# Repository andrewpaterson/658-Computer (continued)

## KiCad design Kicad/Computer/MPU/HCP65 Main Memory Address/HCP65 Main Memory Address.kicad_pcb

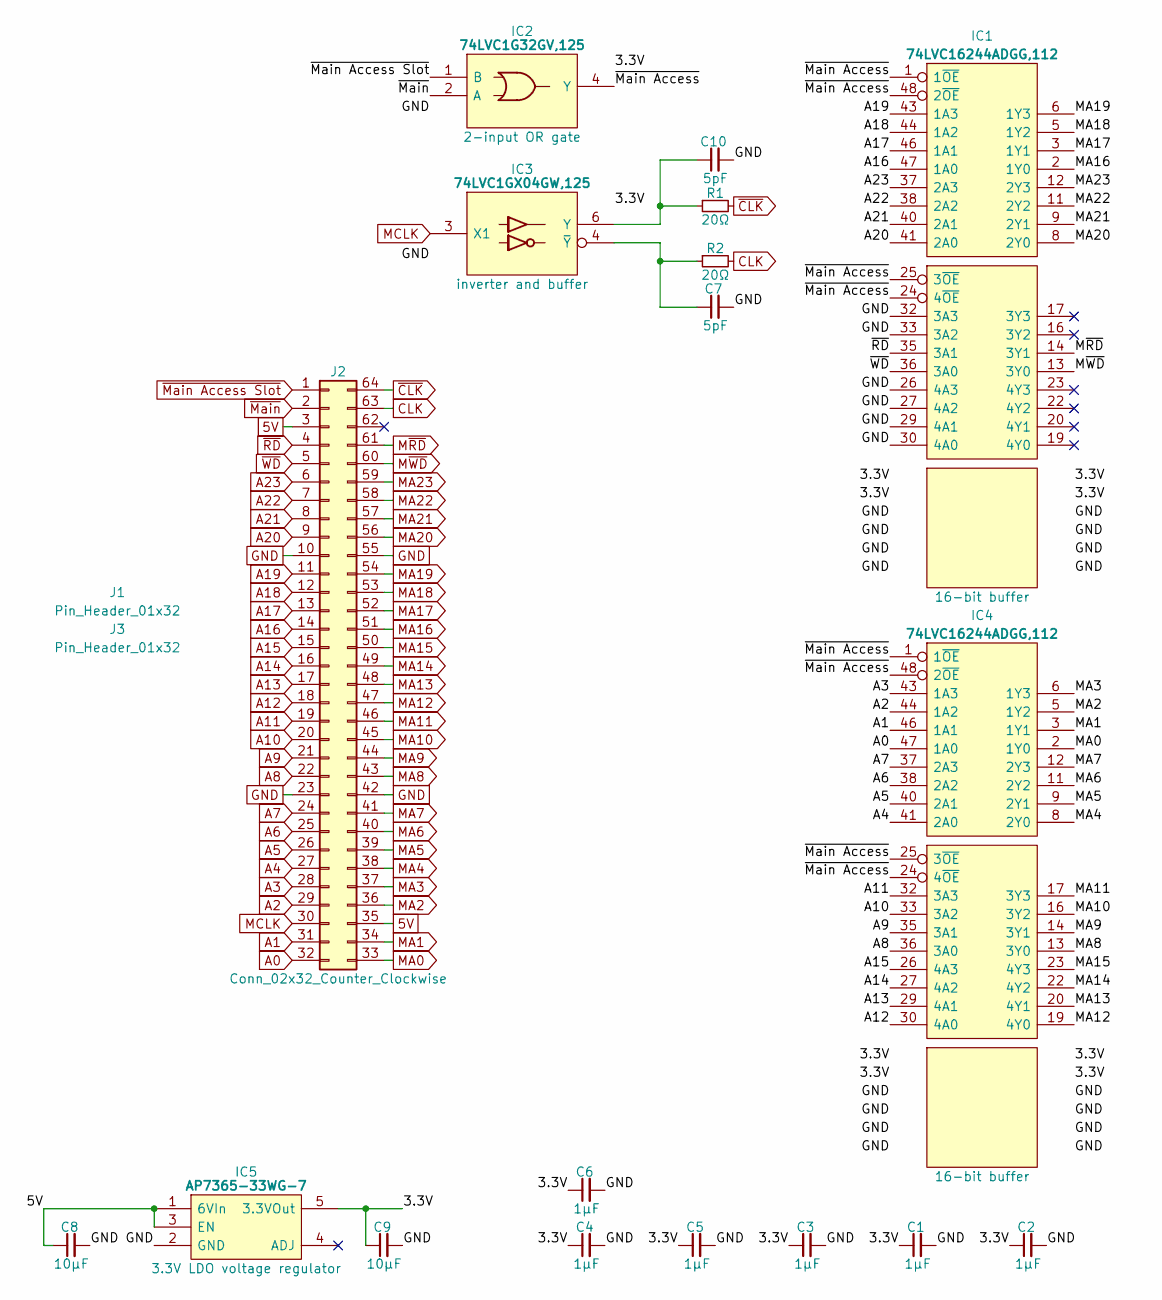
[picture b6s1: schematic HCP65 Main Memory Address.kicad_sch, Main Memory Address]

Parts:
C1, C2, C3, C4, C5, C6: 1μF; C_0805
C7, C10: 5pF; C_0805
C8, C9: 10µF; C_0805
IC1, IC4: 74LVC16244ADGG,112; 74LVC16244ADGG112; Manufacturer_Part_Number 74LVC16244ADGG,112; Mouser Part Number 771-74LVC16244DG
IC2: 74LVC1G32GV,125; SOT95P275X110-5N; Manufacturer_Part_Number 74LVC1G32GV,125; Mouser Part Number 771-LVC1G32GV125
IC3: 74LVC1GX04GW,125; SOP65P210X110-6N; Manufacturer_Part_Number 74LVC1GX04GW,125; Mouser Part Number 771-74LVC1GX04GW-G
IC5: AP7365-33WG-7; SOT95P285X130-5N; Manufacturer_Part_Number AP7365-33WG-7; Mouser Part Number 621-AP7365-33WG-7
J1, J3: Pin_Header_01x32; PinHeader_1x32_P2.54mm_Vertical
J2: Conn_02x32_Counter_Clockwise; DIP-64_Board_W15.24mm
R1, R2: 20Ω; R_0805

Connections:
5V: C8.1, IC5.1 (6VIn), IC5.3 (EN), J2.3, J2.35
/3.3V: C1.1, C2.1, C3.1, C4.1, C5.1, C6.1, C9.1, IC1.7 (3V), IC1.18 (3V), IC1.31 (3V), IC1.42 (3V), IC2.5 (3V), IC3.5 (3V), IC4.7 (3V), IC4.18 (3V), IC4.31 (3V), IC4.42 (3V), IC5.5 (3.3VOut)
/~Main Access: IC1.1 (1~OE), IC1.24 (4~OE), IC1.25 (3~OE), IC1.48 (2~OE), IC2.4 (Y), IC4.1 (1~OE), IC4.24 (4~OE), IC4.25 (3~OE), IC4.48 (2~OE)
A0: IC4.47 (1A0), J2.32
A1: IC4.46 (1A1), J2.31
A2: IC4.44 (1A2), J2.29
A3: IC4.43 (1A3), J2.28
A4: IC4.41 (2A0), J2.27
A5: IC4.40 (2A1), J2.26
A6: IC4.38 (2A2), J2.25
A7: IC4.37 (2A3), J2.24
A8: IC4.36 (3A0), J2.22
A9: IC4.35 (3A1), J2.21
A10: IC4.33 (3A2), J2.20
A11: IC4.32 (3A3), J2.19
A12: IC4.30 (4A0), J2.18
A13: IC4.29 (4A1), J2.17
A14: IC4.27 (4A2), J2.16
A15: IC4.26 (4A3), J2.15
A16: IC1.47 (1A0), J2.14
A17: IC1.46 (1A1), J2.13
A18: IC1.44 (1A2), J2.12
A19: IC1.43 (1A3), J2.11
A20: IC1.41 (2A0), J2.9
A21: IC1.40 (2A1), J2.8
A22: IC1.38 (2A2), J2.7
A23: IC1.37 (2A3), J2.6
CLK: J2.63, R2.2
GND: C1.2, C2.2, C3.2, C4.2, C5.2, C6.2, C7.2, C8.2, C9.2, C10.2, IC1.4 (GND), IC1.10 (GND), IC1.15 (GND), IC1.21 (GND), IC1.26 (4A3), IC1.27 (4A2), IC1.28 (GND), IC1.29 (4A1), IC1.30 (4A0), IC1.32 (3A3), IC1.33 (3A2), IC1.34 (GND), IC1.39 (GND), IC1.45 (GND), IC2.3 (GND), IC3.2 (GND), IC4.4 (GND), IC4.10 (GND), IC4.15 (GND), IC4.21 (GND), IC4.28 (GND), IC4.34 (GND), IC4.39 (GND), IC4.45 (GND), IC5.2 (GND), J2.10, J2.23, J2.42, J2.55
MA0: IC4.2 (1Y0), J2.33
MA1: IC4.3 (1Y1), J2.34
MA2: IC4.5 (1Y2), J2.36
MA3: IC4.6 (1Y3), J2.37
MA4: IC4.8 (2Y0), J2.38
MA5: IC4.9 (2Y1), J2.39
MA6: IC4.11 (2Y2), J2.40
MA7: IC4.12 (2Y3), J2.41
MA8: IC4.13 (3Y0), J2.43
MA9: IC4.14 (3Y1), J2.44
MA10: IC4.16 (3Y2), J2.45
MA11: IC4.17 (3Y3), J2.46
MA12: IC4.19 (4Y0), J2.47
MA13: IC4.20 (4Y1), J2.48
MA14: IC4.22 (4Y2), J2.49
MA15: IC4.23 (4Y3), J2.50
MA16: IC1.2 (1Y0), J2.51
MA17: IC1.3 (1Y1), J2.52
MA18: IC1.5 (1Y2), J2.53
MA19: IC1.6 (1Y3), J2.54
MA20: IC1.8 (2Y0), J2.56
MA21: IC1.9 (2Y1), J2.57
MA22: IC1.11 (2Y2), J2.58
MA23: IC1.12 (2Y3), J2.59
MCLK: IC3.3 (X1), J2.30
M~RD: IC1.14 (3Y1), J2.61
M~WD: IC1.13 (3Y0), J2.60
unnamed: C10.1, IC3.6 (Y), R1.1
unnamed: C7.1, IC3.4 (~Y), R2.1
~CLK: J2.64, R1.2
~Main Access Slot: IC2.1 (B), J2.1
~Main: IC2.2 (A), J2.2
~RD: IC1.35 (3A1), J2.4
~WD: IC1.36 (3A0), J2.5

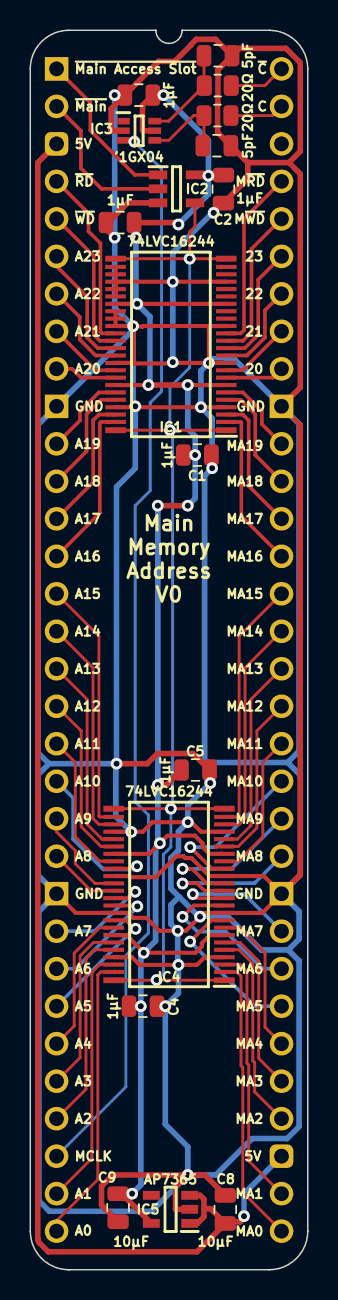
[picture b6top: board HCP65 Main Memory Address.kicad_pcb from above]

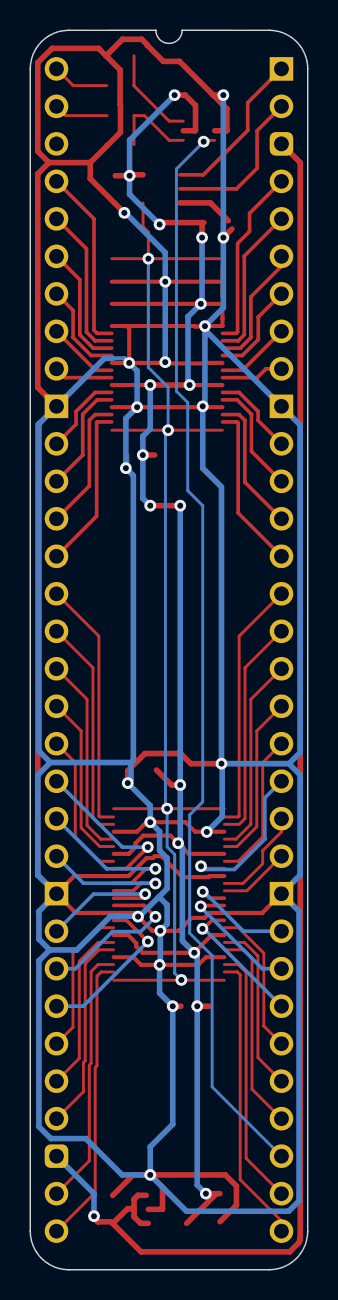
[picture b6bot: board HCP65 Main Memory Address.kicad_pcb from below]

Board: 2 copper layers, 18.8 x 84.0 mm, 20 parts (2 on the bottom side), 63 nets.

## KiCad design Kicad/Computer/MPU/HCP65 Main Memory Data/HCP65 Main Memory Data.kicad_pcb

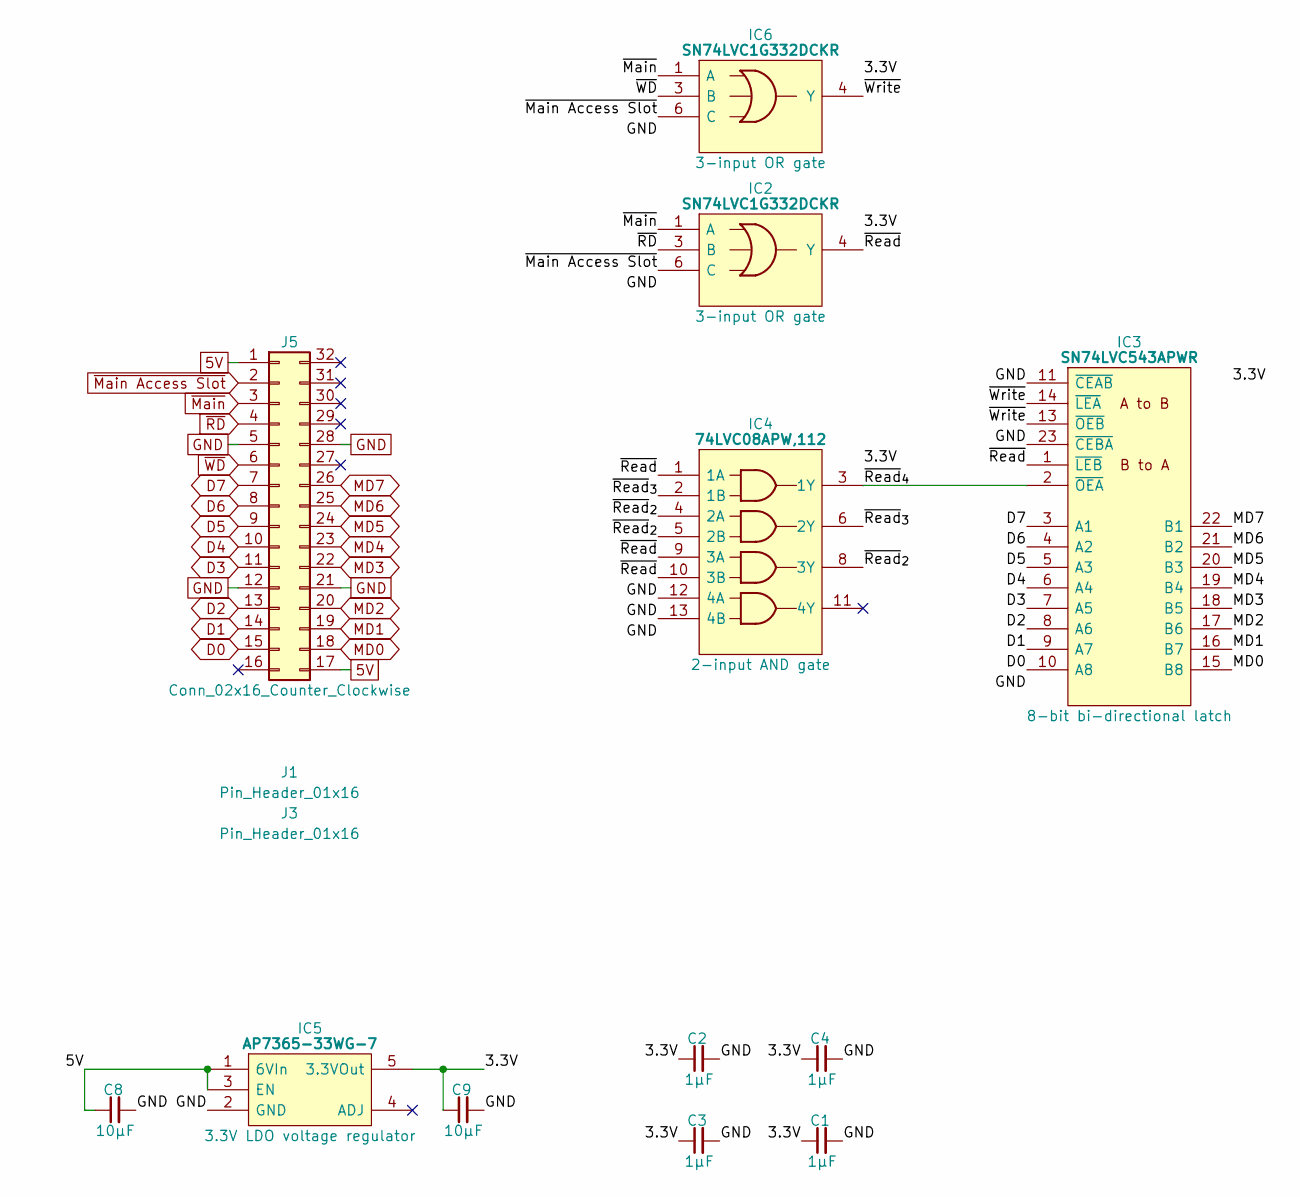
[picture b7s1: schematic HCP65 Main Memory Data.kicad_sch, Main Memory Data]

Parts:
C1, C2, C3, C4: 1μF; C_0805
C8, C9: 10µF; C_0805
IC2, IC6: SN74LVC1G332DCKR; SOT65P210X110-6N; Mouser Part Number 595-SN74LVC1G332DCKR
IC3: SN74LVC543APWR; SOP65P640X120-24N; Mouser Part Number 595-SN74LVC543APWR
IC4: 74LVC08APW,112; SOP65P640X110-14N; Manufacturer_Part_Number 74LVC08APW,112; Mouser Part Number 771-74LVC08APW
IC5: AP7365-33WG-7; SOT95P285X130-5N; Manufacturer_Part_Number AP7365-33WG-7; Mouser Part Number 621-AP7365-33WG-7
J1, J3: Pin_Header_01x16; PinHeader_1x16_P2.54mm_Vertical
J5: Conn_02x16_Counter_Clockwise; DIP-32_Board_W15.24mm

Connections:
5V: C8.1, IC5.1 (6VIn), IC5.3 (EN), J5.1, J5.17
/3.3V: C1.1, C2.1, C3.1, C4.1, C9.1, IC2.5 (3V), IC3.24 (3V), IC4.14 (3V), IC5.5 (3.3VOut), IC6.5 (3V)
/~Read: IC2.4 (Y), IC3.1 (~LEB), IC4.1 (1A), IC4.9 (3A), IC4.10 (3B)
/~Read_{2}: IC4.4 (2A), IC4.5 (2B), IC4.8 (3Y)
/~Read_{3}: IC4.2 (1B), IC4.6 (2Y)
/~Read_{4}: IC3.2 (~OEA), IC4.3 (1Y)
/~Write: IC3.13 (~OEB), IC3.14 (~LEA), IC6.4 (Y)
D0: IC3.10 (A8), J5.15
D1: IC3.9 (A7), J5.14
D2: IC3.8 (A6), J5.13
D3: IC3.7 (A5), J5.11
D4: IC3.6 (A4), J5.10
D5: IC3.5 (A3), J5.9
D6: IC3.4 (A2), J5.8
D7: IC3.3 (A1), J5.7
GND: C1.2, C2.2, C3.2, C4.2, C8.2, C9.2, IC2.2 (GND), IC3.11 (~CEAB), IC3.12 (GND), IC3.23 (~CEBA), IC4.7 (GND), IC4.12 (4A), IC4.13 (4B), IC5.2 (GND), IC6.2 (GND), J5.5, J5.12, J5.21, J5.28
MD0: IC3.15 (B8), J5.18
MD1: IC3.16 (B7), J5.19
MD2: IC3.17 (B6), J5.20
MD3: IC3.18 (B5), J5.22
MD4: IC3.19 (B4), J5.23
MD5: IC3.20 (B3), J5.24
MD6: IC3.21 (B2), J5.25
MD7: IC3.22 (B1), J5.26
~Main Access Slot: IC2.6 (C), IC6.6 (C), J5.2
~Main: IC2.1 (A), IC6.1 (A), J5.3
~RD: IC2.3 (B), J5.4
~WD: IC6.3 (B), J5.6

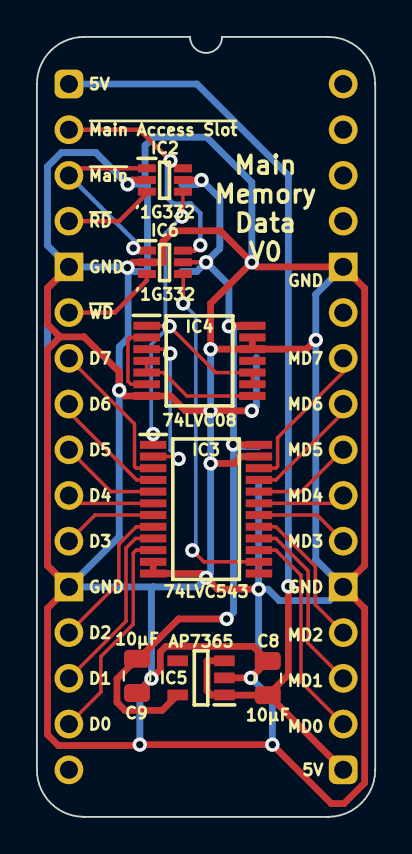
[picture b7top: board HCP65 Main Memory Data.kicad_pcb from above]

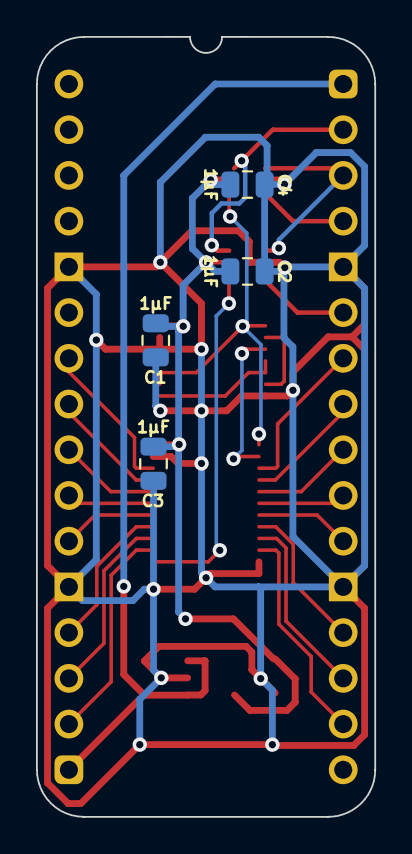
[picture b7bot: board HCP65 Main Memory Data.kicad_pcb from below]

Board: 2 copper layers, 18.8 x 43.3 mm, 14 parts (6 on the bottom side), 28 nets.

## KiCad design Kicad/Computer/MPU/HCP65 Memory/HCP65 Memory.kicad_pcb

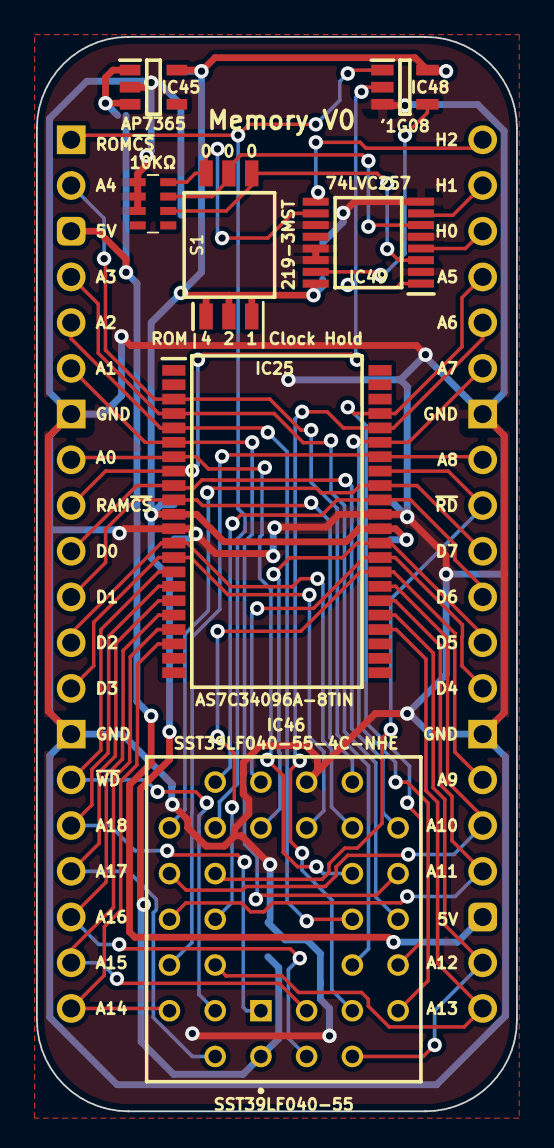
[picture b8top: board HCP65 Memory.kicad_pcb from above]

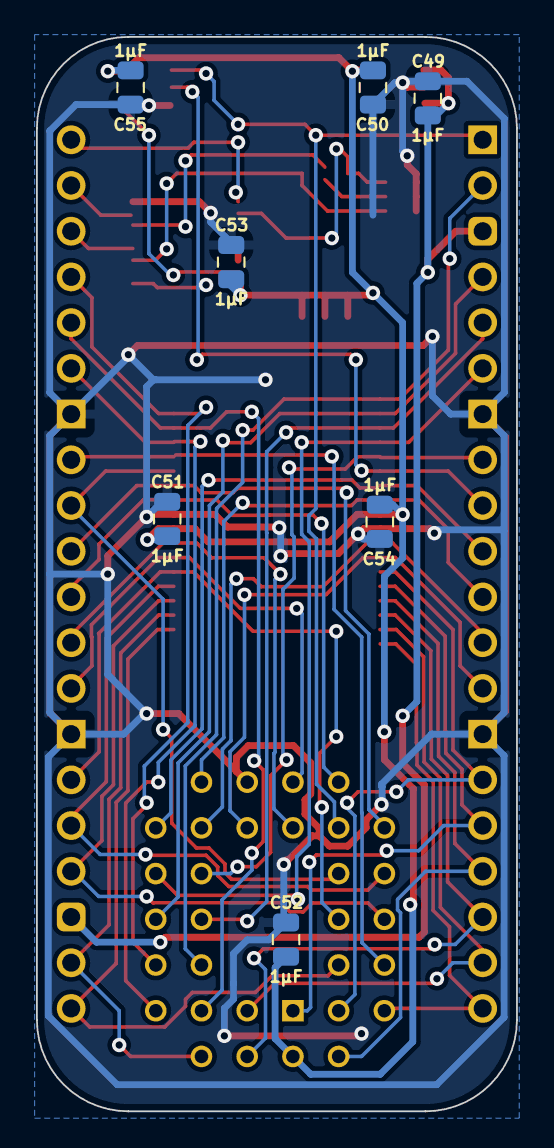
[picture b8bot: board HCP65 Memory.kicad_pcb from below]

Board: 2 copper layers, 26.7 x 59.7 mm, 15 parts (7 on the bottom side), 41 nets.

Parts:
C49, C50, C51, C52, C53, C54, C55: 1μF; C_0805
IC25: AS7C34096A-8TIN; SOP80P1176X120-44N
IC45: AP7365-33WG-7; SOT95P285X130-5N
IC46: SST39LF040-55-4C-NHE; 5408803224008
IC48: 74LVC1G08GV,125; SOT95P275X110-5N
IC49: 74LVC257APW,118; SOP65P640X110-16N
J8: Conn_02x20_Counter_Clockwise; DIP-40_Board_W22.86mm
RN3: CAY16-103J4LF; CAY16-J4
S1: 219-3MST; SOIC127P844X265-6N

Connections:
/Memory Board/3.3V: C50.1, C51.1, C52.1, C53.1, C54.1, C55.1, IC25.11 (3V), IC25.33 (3V), IC45.5 (VOUT), IC46.32 (3V), IC48.5 (3V), IC49.16 (3V), S1.1, S1.2, S1.3
/Memory Board/5V: C49.1, IC45.1 (VIN), IC45.3 (EN), J8.3, J8.23
/Memory Board/A0: IC25.7 (A0), IC46.12 (A0), J8.8
/Memory Board/A1: IC25.6 (A1), IC46.11 (A1), J8.6
/Memory Board/A2: IC25.5 (A2), IC46.10 (A2), J8.5
/Memory Board/A3: IC25.4 (A3), IC46.9 (A3), J8.4
/Memory Board/A4: IC25.3 (A4), IC46.8 (A4), J8.2
/Memory Board/A5: IC25.41 (A5), IC46.7 (A5), J8.37
/Memory Board/A6: IC25.40 (A6), IC46.6 (A6), J8.36
/Memory Board/A7: IC25.39 (A7), IC46.5 (A7), J8.35
/Memory Board/A8: IC25.38 (A8), IC46.27 (A8), J8.33
/Memory Board/A9: IC25.30 (A9), IC46.26 (A9), J8.26
/Memory Board/A10: IC25.29 (A10), IC46.23 (A10), J8.25
/Memory Board/A11: IC25.28 (A11), IC46.25 (A11), J8.24
/Memory Board/A12: IC25.27 (A12), IC46.4 (A12), J8.22
/Memory Board/A13: IC25.26 (A13), IC46.28 (A13), J8.21
/Memory Board/A14: IC25.20 (A14), IC46.29 (A14), J8.20
/Memory Board/A15: IC25.19 (A15), IC46.3 (A15), J8.19
/Memory Board/A16: IC25.18 (A16), IC46.2 (A16), J8.18
/Memory Board/A17: IC25.17 (A17), IC46.30 (A17), J8.17
/Memory Board/A18: IC25.16 (A18), IC46.1 (A18), J8.16
/Memory Board/CH0_{OUT}: IC49.4 (1Y), J8.38
/Memory Board/CH1_{OUT}: IC49.7 (2Y), J8.39
/Memory Board/CH2_{OUT}: IC49.9 (3Y), J8.40
/Memory Board/D0: IC25.9 (DQ0), IC46.13 (DQ0), J8.10
/Memory Board/D1: IC25.10 (DQ1), IC46.14 (DQ1), J8.11
/Memory Board/D2: IC25.13 (DQ2), IC46.15 (DQ2), J8.12
/Memory Board/D3: IC25.14 (DQ3), IC46.17 (DQ3), J8.13
/Memory Board/D4: IC25.31 (DQ4), IC46.18 (DQ4), J8.28
/Memory Board/D5: IC25.32 (DQ5), IC46.19 (DQ5), J8.29
/Memory Board/D6: IC25.35 (DQ6), IC46.20 (DQ6), J8.30
/Memory Board/D7: IC25.36 (DQ7), IC46.21 (DQ7), J8.31
/Memory Board/GND: C49.2, C50.2, C51.2, C52.2, C53.2, C54.2, C55.2, IC25.12 (GND), IC25.34 (GND), IC45.2 (GND), IC46.16 (GND), IC48.3 (GND), IC49.2 (1I0), IC49.5 (2I0), IC49.8 (GND), IC49.11 (3I0), IC49.13 (4I1), IC49.14 (4I0), J8.7, J8.14, J8.27, J8.34, RN3.1 (R1), RN3.2 (R2), RN3.3 (R3)
/Memory Board/SW_{0}: IC49.3 (1I1), RN3.6 (R3), S1.4
/Memory Board/SW_{1}: IC49.6 (2I1), RN3.7 (R2), S1.5
/Memory Board/SW_{2}: IC49.10 (3I1), RN3.8 (R1), S1.6
/Memory Board/~RAM_{CS}: IC25.8 (~CE), IC48.2 (A), IC49.1 (S), J8.9
/Memory Board/~RAM_{CS}·~ROM_{CS}: IC48.4 (Y), IC49.15 (~OE)
/Memory Board/~RD: IC25.37 (~OE), IC46.24 (~OE), J8.32
/Memory Board/~ROM_{CS}: IC46.22 (~CE), IC48.1 (B), J8.1
/Memory Board/~WD: IC25.15 (~WE), IC46.31 (~WE), J8.15
